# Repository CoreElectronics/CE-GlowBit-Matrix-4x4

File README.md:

# GlowBit™ Matrix 4x4

This is the repo for the Core Electronics [GlowBit Matrix 4x4](https://core-electronics.com.au/catalog/product/view/sku/ce08031).

## License
This project is open source - please review the LICENSE.md file for further licensing information.

If you have any technical questions, or concerns about licensing, please contact technical support on the [Core Electronics forums](https://forum.core-electronics.com.au/).

*\"GlowBit\" and the GlowBit logo are trademarks of Core Electronics Pty Ltd.*

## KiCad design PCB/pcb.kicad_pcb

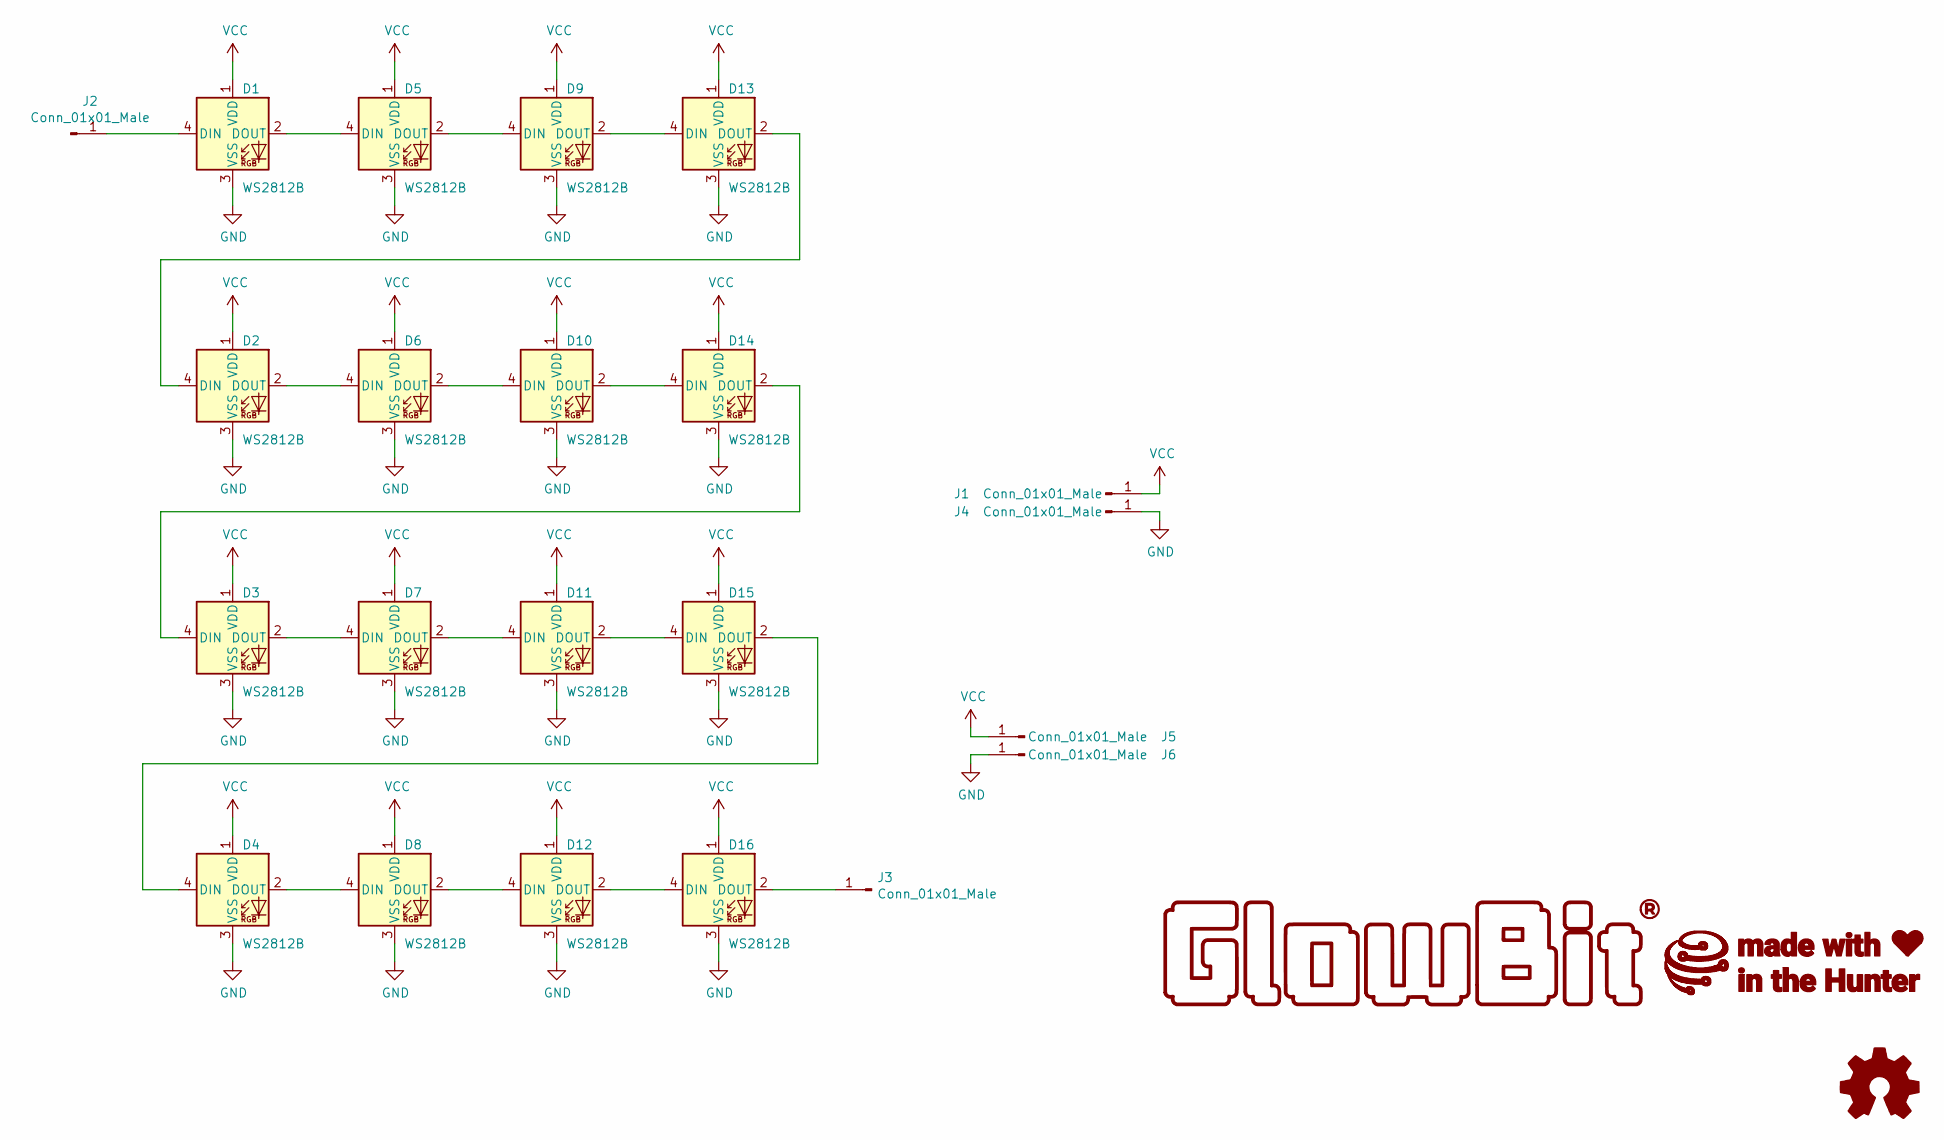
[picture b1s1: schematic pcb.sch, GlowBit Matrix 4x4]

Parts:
D1, D2, D3, D4, D5, D6, D7, D8, D9, D10, D11, D12, D13, D14, D15, D16: WS2812B; LED_GlowBit_WS2812B_NoSilk
J1, J2, J3, J4, J5, J6: Conn_01x01_Male; PinHeader_1x01_P2.54mm_Vertical

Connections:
GND: D1.3 (VSS), D2.3 (VSS), D3.3 (VSS), D4.3 (VSS), D5.3 (VSS), D6.3 (VSS), D7.3 (VSS), D8.3 (VSS), D9.3 (VSS), D10.3 (VSS), D11.3 (VSS), D12.3 (VSS), D13.3 (VSS), D14.3 (VSS), D15.3 (VSS), D16.3 (VSS), J4.1, J6.1
unnamed: D1.2 (DOUT), D5.4 (DIN)
unnamed: D1.4 (DIN), J2.1
unnamed: D2.2 (DOUT), D6.4 (DIN)
unnamed: D3.2 (DOUT), D7.4 (DIN)
unnamed: D4.2 (DOUT), D8.4 (DIN)
unnamed: D5.2 (DOUT), D9.4 (DIN)
unnamed: D10.2 (DOUT), D14.4 (DIN)
unnamed: D6.2 (DOUT), D10.4 (DIN)
unnamed: D11.2 (DOUT), D15.4 (DIN)
unnamed: D7.2 (DOUT), D11.4 (DIN)
unnamed: D12.2 (DOUT), D16.4 (DIN)
unnamed: D8.2 (DOUT), D12.4 (DIN)
unnamed: D2.4 (DIN), D13.2 (DOUT)
unnamed: D9.2 (DOUT), D13.4 (DIN)
unnamed: D3.4 (DIN), D14.2 (DOUT)
unnamed: D4.4 (DIN), D15.2 (DOUT)
unnamed: D16.2 (DOUT), J3.1
VCC: D1.1 (VDD), D2.1 (VDD), D3.1 (VDD), D4.1 (VDD), D5.1 (VDD), D6.1 (VDD), D7.1 (VDD), D8.1 (VDD), D9.1 (VDD), D10.1 (VDD), D11.1 (VDD), D12.1 (VDD), D13.1 (VDD), D14.1 (VDD), D15.1 (VDD), D16.1 (VDD), J1.1, J5.1

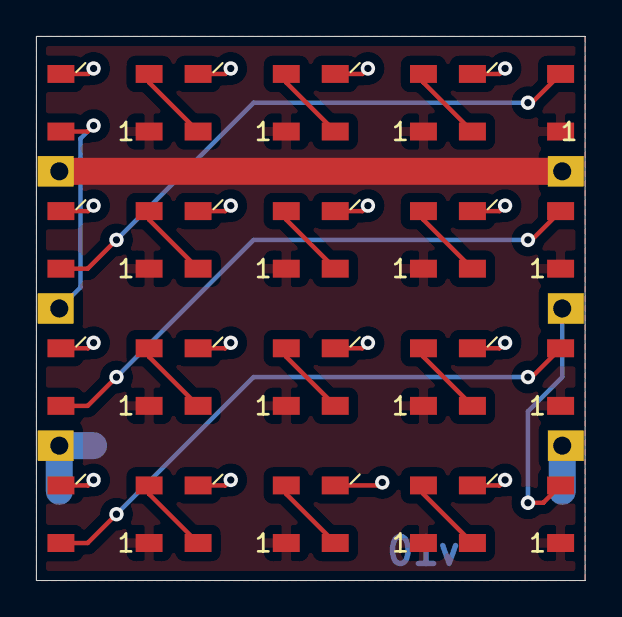
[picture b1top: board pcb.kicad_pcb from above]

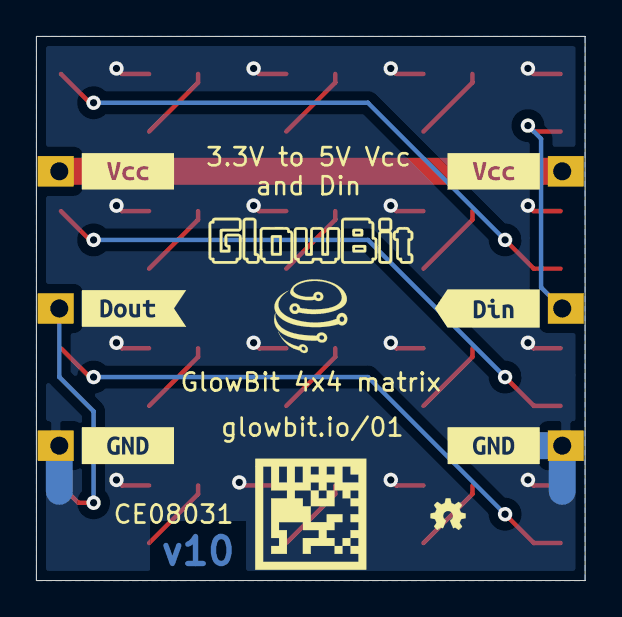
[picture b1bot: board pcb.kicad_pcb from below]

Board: 2 copper layers, 30.5 x 30.2 mm, 28 parts (6 on the bottom side), 19 nets.

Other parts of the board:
kibuzzard-6119FB4C, kibuzzard-6119FB06, kibuzzard-6119FB8F, kibuzzard-6119FB8F#2, kibuzzard-6119FBA7, kibuzzard-6119FBA7#2: G***; label

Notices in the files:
PCB/pcb.kicad_pcb:
License: CCASAv4.0 https://creativecommons.org/licenses/by-sa/4.0
